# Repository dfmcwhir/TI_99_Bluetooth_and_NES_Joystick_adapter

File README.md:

<h2>Bluetooth and NES controller to TI99/4A joystick port adapter.</h2>
<p>
Uses Bluepad32 with the Arduino IDE on a WEMOS ESP32 D1 board. See https://bluepad32.readthedocs.io/en/latest/plat_arduino/ for Bluepad32 installation instructions. The NES gamepad code is based on the NESControllerInterface library by https://harryslab.net/nes-controller-breakout-board/ for the NES controllers </p>
<p>
Boards made by and available from PCBWay.com: <br>
https://www.pcbway.com/project/shareproject/TI99_4a_Bluetooth_and_NES_Joystick_Adapter_bd76dbdd.html</p>

<h2>Theory of operation</h2>
<p>
The TI99/4A's joystick port scans the up,down,left,right, and fire signals using two joystick scan lines (one for each joystick), similar to the way it scans the keyboard rows and columns. So to interface with that circuit, the ESP32 control analog switch ICs (CD4066) to simulate the connection between the scan lines the input signals the same way a button being pressed on a stock controller would.</p>

<h2>Connecting the adapter</h2>
<p>In order to plug the adapter directly into the joystick port on the TI99, the two standoff on the DB9 of the adapter have to be removed. I couldn't find a source for a right angle DB9 that didn't have standoff on them. If plugging directly into the TI99, it would be recommended to have the TI99 on a flat, level surface and then put something under the adapter so that it is at the same level of the TI99. Otherwise there will be a fair amount of weight hanging off the connector and it might fall out or wear out the connectors. A better idea is probably to connect the adapter to the TI99 with a short DB9 cable.</p> 
<p>Power is supplied to the barrel jack from a 5V, center positive, wall wart. Something like what you might find for powering an old wifi router.</p>

<h2>Operation</h2>
<p>There are two push buttons and two switches on the adapter. The JButton is on the side of the adapter (with the NES ports facing you) and towards the back. That button is pressed for binding a bluetooth controller. Holding it for more than 2 seconds will cause the adapter to forget bound BT controllers. The Reset button is the side button closer to the front just resets the adapter. The switch on the top, closest to the power input jack is the power on-off switch. The other switch on the top, closer to the front of the adapter switches between using the NES gamepads or BT controllers. It is only checked on power up, so to switch between modes, set it to the mode you want and then power up the adapter.</p>

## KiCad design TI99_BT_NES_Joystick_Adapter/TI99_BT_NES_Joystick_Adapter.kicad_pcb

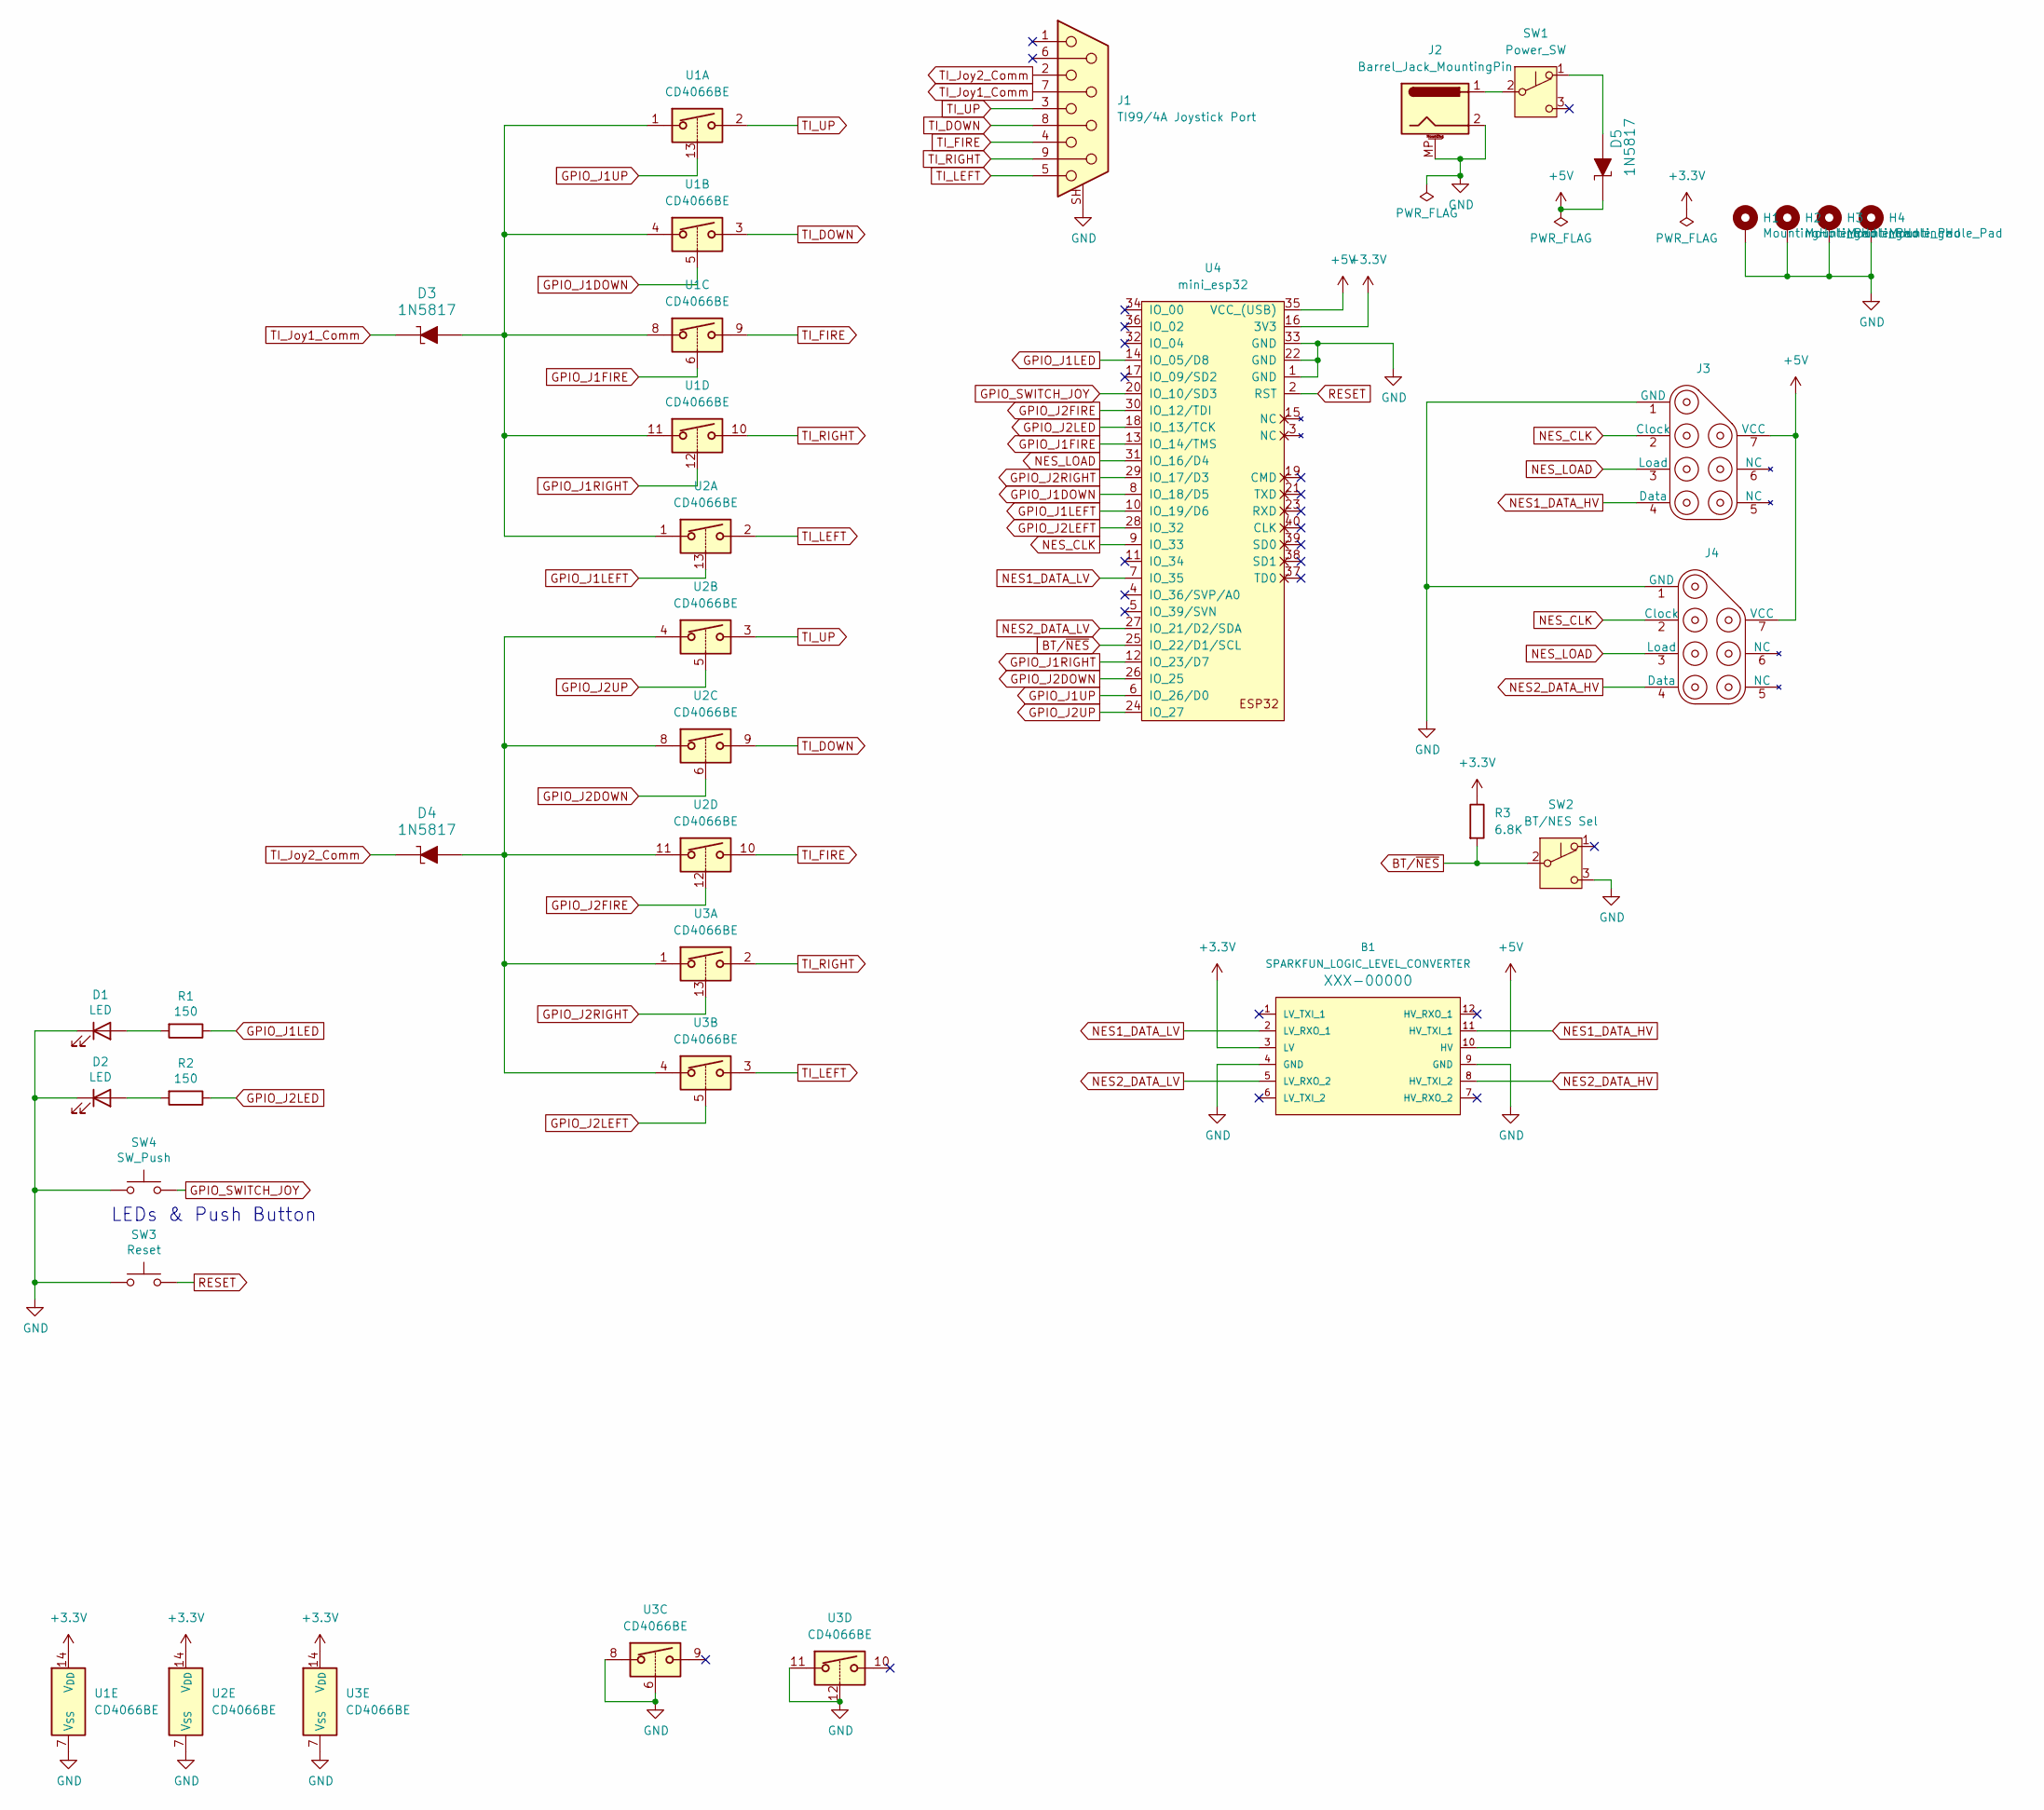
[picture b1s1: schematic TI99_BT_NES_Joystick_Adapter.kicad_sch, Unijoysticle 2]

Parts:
B1: SPARKFUN_LOGIC_LEVEL_CONVERTER; 4_Chan_Logic_level_shifter_module
D1, D2: LED; LED_3mm_Radial
D3, D4, D5: 1N5817; DO-41; MPN 1N5817; Digi-Key_PN 1N5817FSCT-ND
H1, H2, H3, H4: MountingHole_Pad; MountingHole_2.7mm_M2.5_DIN965_Pad
J1: TI99/4A Joystick Port; DSUB-9_Socket_Horizontal_P2.77x2.84mm_EdgePinOffset7.70mm_H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
J2: Barrel_Jack_MountingPin; BarrelJack_Horizontal
J3, J4: NES_Controller_Port
R1, R2: 150; R_Axial_DIN0204_L3.6mm_D1.6mm_P7.62mm_Horizontal
R3: 6.8K; R_Axial_DIN0204_L3.6mm_D1.6mm_P7.62mm_Horizontal
SW1: Power_SW; SW_Slide-03_pins123_10x2.5x6.4_P2.54mm
SW2: BT/NES Sel; SW_Slide-03_pins123_10x2.5x6.4_P2.54mm
SW3: Reset; SW_Tactile_SPST_Angled_PTS645Vx39-2LFS
SW4: SW_Push; SW_Tactile_SPST_Angled_PTS645Vx39-2LFS
U1, U2, U3: CD4066BE; DIP-14_W7.62mm
U4: mini_esp32; ESP32_mini

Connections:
3.3V: B1.3 (LV), R3.1, U1.14 (V_{DD}), U2.14 (V_{DD}), U3.14 (V_{DD}), U4.16 (3V3)
5V: B1.10 (HV), D5.K, J3.7 (VCC), J4.7 (VCC), U4.35 (VCC_(USB))
BT/~NES: R3.2, SW2.2 (B), U4.25 (IO_22/D1/SCL)
GND: B1.4 (GND), B1.9 (GND), D1.1 (K), D2.1 (K), H1.1 (1_1), H2.1 (1_1), H3.1 (1_1), H4.1 (1_1), J1.SH (PAD), J2.2, J2.MP (MountPin), J3.1 (GND), J4.1 (GND), SW2.3 (C), SW3.1, SW4.1, U1.7 (V_{SS}), U2.7 (V_{SS}), U3.6, U3.7 (V_{SS}), U3.8, U3.11, U3.12, U4.1 (GND), U4.22 (GND), U4.33 (GND)
GPIO_J1DOWN: U1.5, U4.8 (IO_18/D5)
GPIO_J1FIRE: U1.6, U4.13 (IO_14/TMS)
GPIO_J1LED: R1.1, U4.14 (IO_05/D8)
GPIO_J1LEFT: U2.13, U4.10 (IO_19/D6)
GPIO_J1RIGHT: U1.12, U4.12 (IO_23/D7)
GPIO_J1UP: U1.13, U4.6 (IO_26/D0)
GPIO_J2DOWN: U2.6, U4.26 (IO_25)
GPIO_J2FIRE: U2.12, U4.30 (IO_12/TDI)
GPIO_J2LED: R2.1, U4.18 (IO_13/TCK)
GPIO_J2LEFT: U3.5, U4.28 (IO_32)
GPIO_J2RIGHT: U3.13, U4.29 (IO_17/D3)
GPIO_J2UP: U2.5, U4.24 (IO_27)
GPIO_SWITCH_JOY: SW4.2, U4.20 (IO_10/SD3)
NES1_DATA_HV: B1.11 (HV_TXI_1), J3.4 (Data)
NES1_DATA_LV: B1.2 (LV_RXO_1), U4.7 (IO_35)
NES2_DATA_HV: B1.8 (HV_TXI_2), J4.4 (Data)
NES2_DATA_LV: B1.5 (LV_RXO_2), U4.27 (IO_21/D2/SDA)
NES_CLK: J3.2 (Clock), J4.2 (Clock), U4.9 (IO_33)
NES_LOAD: J3.3 (Load), J4.3 (Load), U4.31 (IO_16/D4)
unnamed: D1.2 (A), R1.2
unnamed: D2.2 (A), R2.2
unnamed: D3.A, U1.1, U1.4, U1.8, U1.11, U2.1
unnamed: D4.A, U2.4, U2.8, U2.11, U3.1, U3.4
unnamed: D5.A, SW1.1 (A)
unnamed: J2.1, SW1.2 (B)
RESET: SW3.2, U4.2 (RST)
TI_DOWN: J1.8, U1.3, U2.9
TI_FIRE: J1.4, U1.9, U2.10
TI_Joy1_Comm: D3.K, J1.7
TI_Joy2_Comm: D4.K, J1.2
TI_LEFT: J1.5, U2.2, U3.3
TI_RIGHT: J1.9, U1.10, U3.2
TI_UP: J1.3, U1.2, U2.3

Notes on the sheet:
LEDs & Push Button

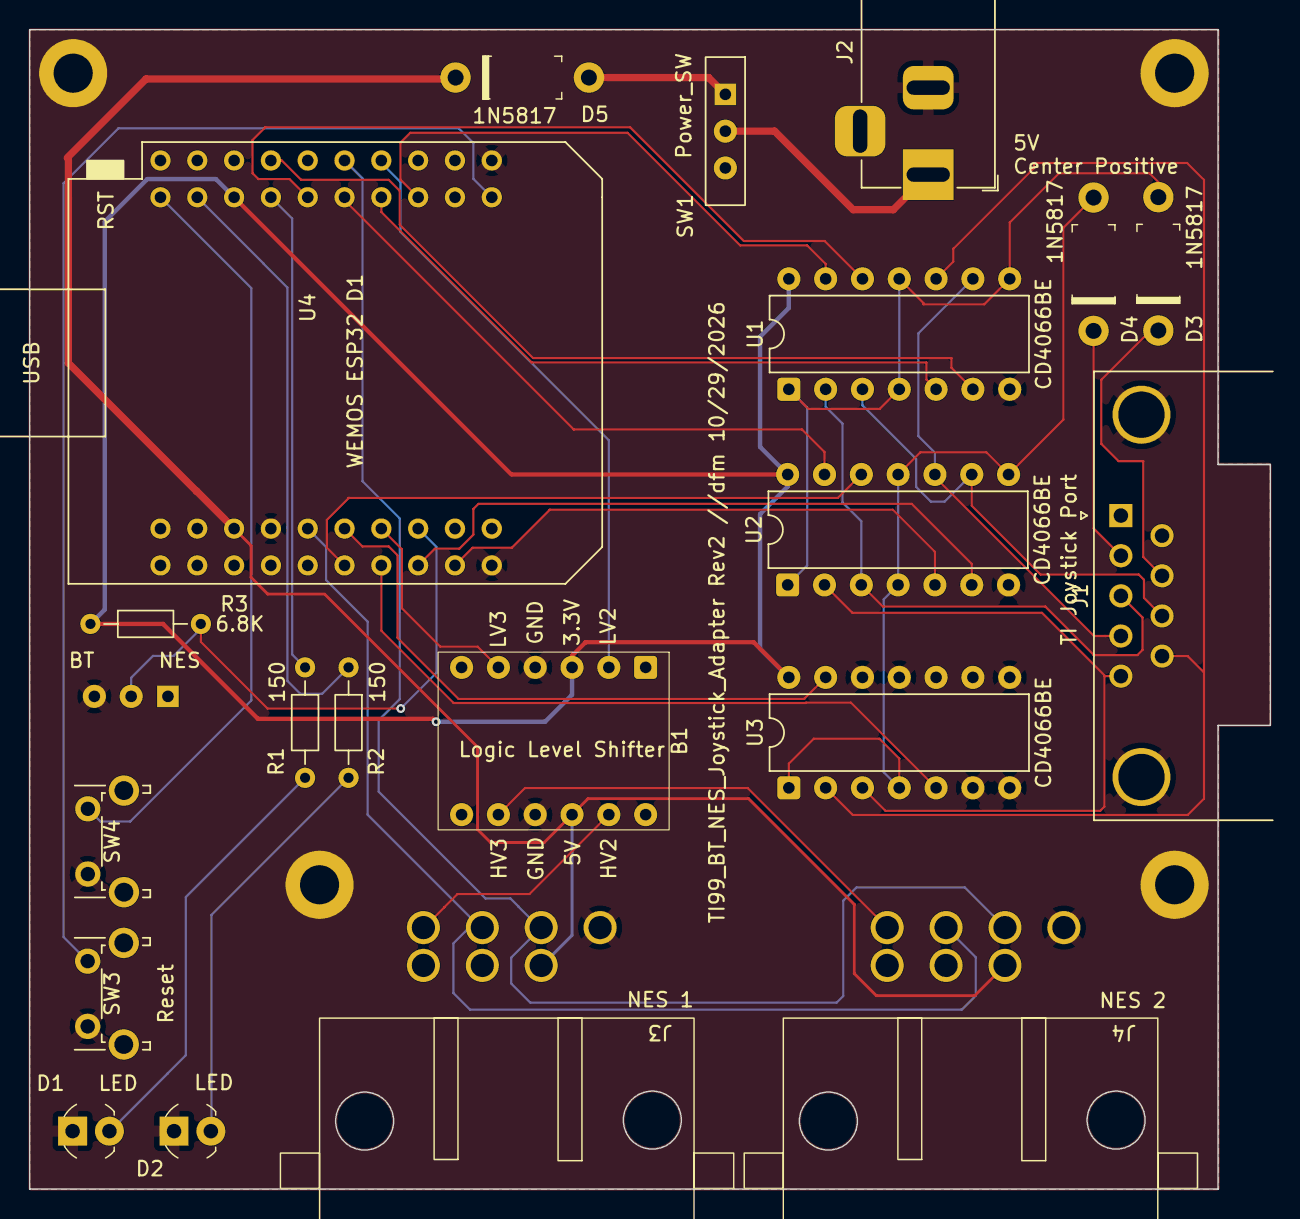
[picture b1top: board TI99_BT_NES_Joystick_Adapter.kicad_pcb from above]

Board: 2 copper layers, 85.6 x 80.0 mm, 25 parts (1 on the bottom side), 37 nets.
